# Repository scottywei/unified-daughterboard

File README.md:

unified-daughterboard-with-power-switch

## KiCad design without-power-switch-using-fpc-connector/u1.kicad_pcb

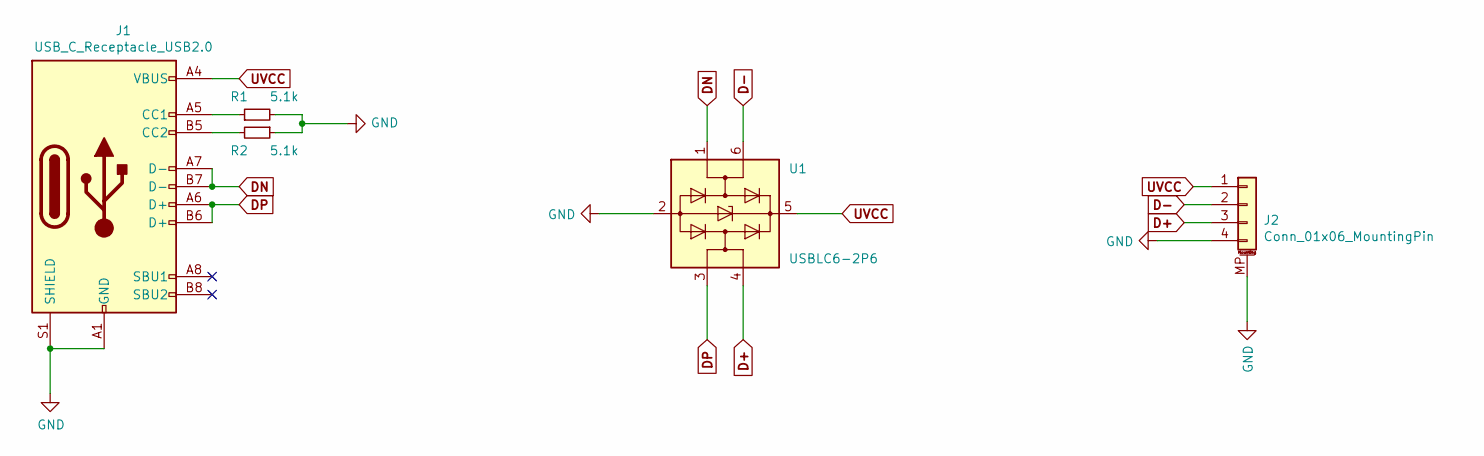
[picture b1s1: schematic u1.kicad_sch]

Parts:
J1: USB_C_Receptacle_USB2.0; USB_C_Receptacle_HRO_TYPE-C-31-M-12
J2: Conn_01x06_MountingPin; FPC_4P_1.0mm
R1, R2: 5.1k; R_0603_1608Metric
U1: USBLC6-2P6; SOT-666

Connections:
D+: J2.3, U1.4 (I/O2)
D-: J2.2, U1.6 (I/O1)
DN: J1.A7 (D-), J1.B7 (D-), U1.1 (I/O1)
DP: J1.A6 (D+), J1.B6 (D+), U1.3 (I/O2)
GND: J1.A1 (GND), J1.A12 (GND), J1.B1 (GND), J1.B12 (GND), J1.S1 (SHIELD), J2.4, J2.MP (MountPin), R1.2, R2.1, U1.2 (GND)
unnamed: J1.A5 (CC1), R1.1
unnamed: J1.B5 (CC2), R2.2
UVCC: J1.A4 (VBUS), J1.A9 (VBUS), J1.B4 (VBUS), J1.B9 (VBUS), J2.1, U1.5 (VBUS)

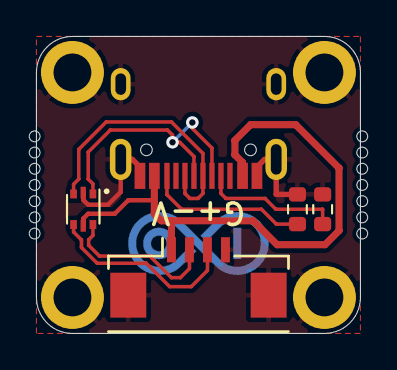
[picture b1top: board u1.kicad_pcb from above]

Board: 2 copper layers, 18.0 x 16.5 mm, 5 parts (0 on the bottom side), 8 nets.

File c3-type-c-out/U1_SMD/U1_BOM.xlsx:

编号 | 值/型号 | 封装 | 数量 | 备注
J1 | USB_C_Receptacle_USB2.0 | USB_C_Receptacle_HRO_TYPE-C-31-M-12 | 1 | https://www.usb.org/sites/default/files/documents/usb_type-c.zip
J2 | JST_SH_SM04B-SRSS | JST_SH_SM04B-SRSS-TB_1x04-1MP_P1.00mm_Horizontal | 1 | ~
R1, R2 | 5.1k | R_0603 | 2 | ~
U1 | USBLC6-2P6 | SOT-666 | 1 | https://www.st.com/resource/en/datasheet/usblc6-2.pdf

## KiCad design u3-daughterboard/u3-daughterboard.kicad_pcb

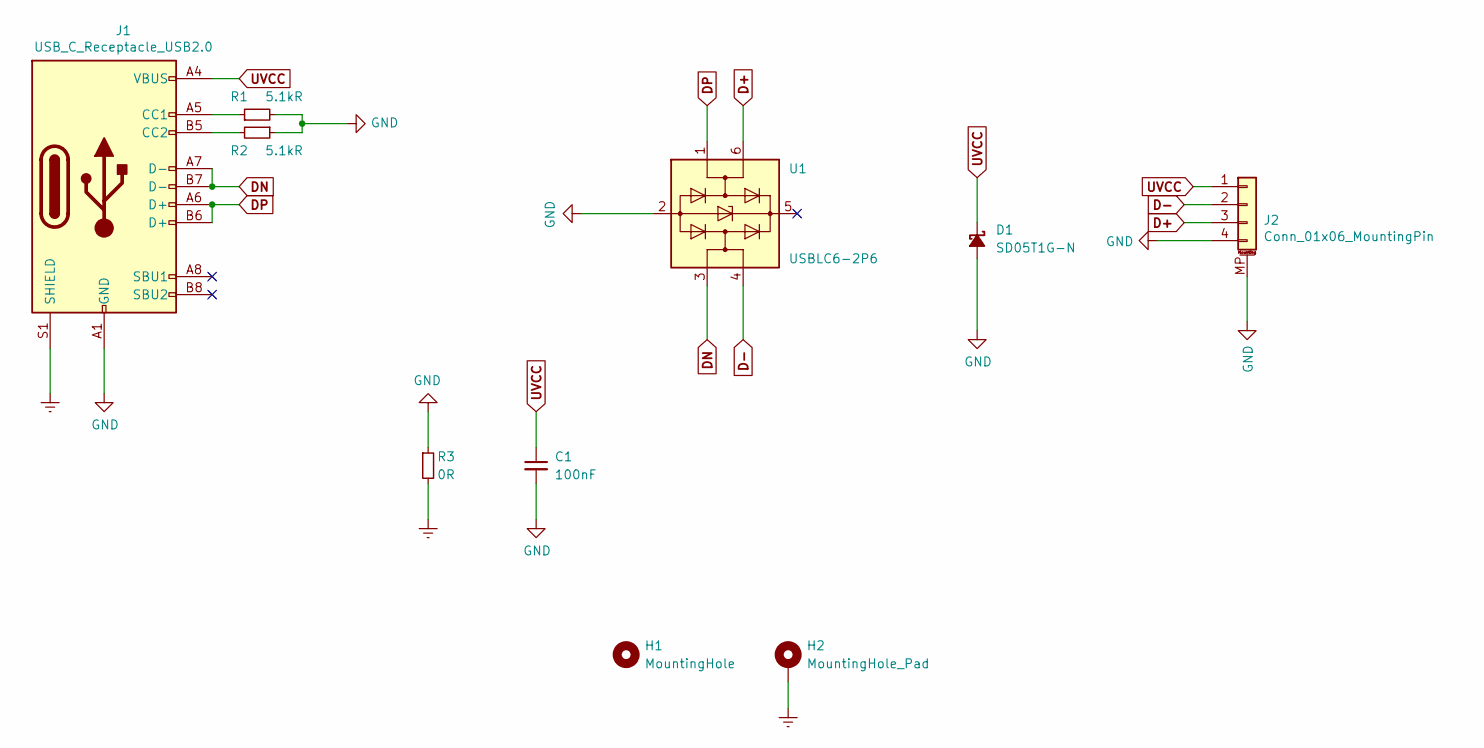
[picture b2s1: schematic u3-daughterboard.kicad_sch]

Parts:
C1: 100nF; C_0402_1005Metric
D1: SD05T1G-N; D_SOD-323
H1: MountingHole; MountingHole_3.2mm_M3
H2: MountingHole_Pad; MountingHole_3.2mm_M3_Pad_TopBottom
J1: USB_C_Receptacle_USB2.0; USB_C_Receptacle_HRO_TYPE-C-31-M-12
J2: Conn_01x06_MountingPin; molex_781710004
R1, R2: 5.1kR; R_0402_1005Metric
R3: 0R; R_0603_1608Metric
U1: USBLC6-2P6; SOT-666

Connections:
D+: J2.3, U1.6 (I/O1)
D-: J2.2, U1.4 (I/O2)
DN: J1.A7 (D-), J1.B7 (D-), U1.3 (I/O2)
DP: J1.A6 (D+), J1.B6 (D+), U1.1 (I/O1)
Earth: H2.1, J1.S1 (SHIELD), R3.2
GND: C1.2, D1.2 (A), J1.A1 (GND), J1.A12 (GND), J1.B1 (GND), J1.B12 (GND), J2.4, J2.MP (MountPin), R1.2, R2.1, R3.1, U1.2 (GND)
unnamed: J1.A5 (CC1), R1.1
unnamed: J1.B5 (CC2), R2.2
UVCC: C1.1, D1.1 (K), J1.A4 (VBUS), J1.A9 (VBUS), J1.B4 (VBUS), J1.B9 (VBUS), J2.1

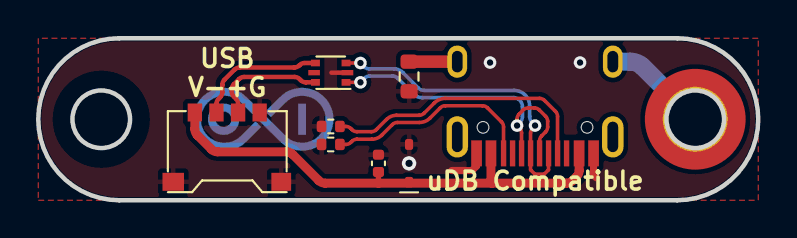
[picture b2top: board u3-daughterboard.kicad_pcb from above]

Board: 2 copper layers, 40.0 x 9.0 mm, 10 parts (0 on the bottom side), 9 nets.

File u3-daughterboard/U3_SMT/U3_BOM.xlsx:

位号 | 值/型号 | 封装 | 数量 | 备注 | Sourced | Model
C1 | 100nF | C_0402 | 1
R1, R2 | 5.1kR | R_0402 | 2
R3 | 0R | R_0603 | 1
D1 | SD05T1G-N | D_SOD-323 | 1
U1 | USBLC6-2P6 | SOT-666 | 1
J1 | USB_C_Receptacle_USB2.0 | USB_C_Receptacle_HRO_TYPE-C-31-M-12 | 1
J2 | molex_781710004 | molex_781710004 | 1

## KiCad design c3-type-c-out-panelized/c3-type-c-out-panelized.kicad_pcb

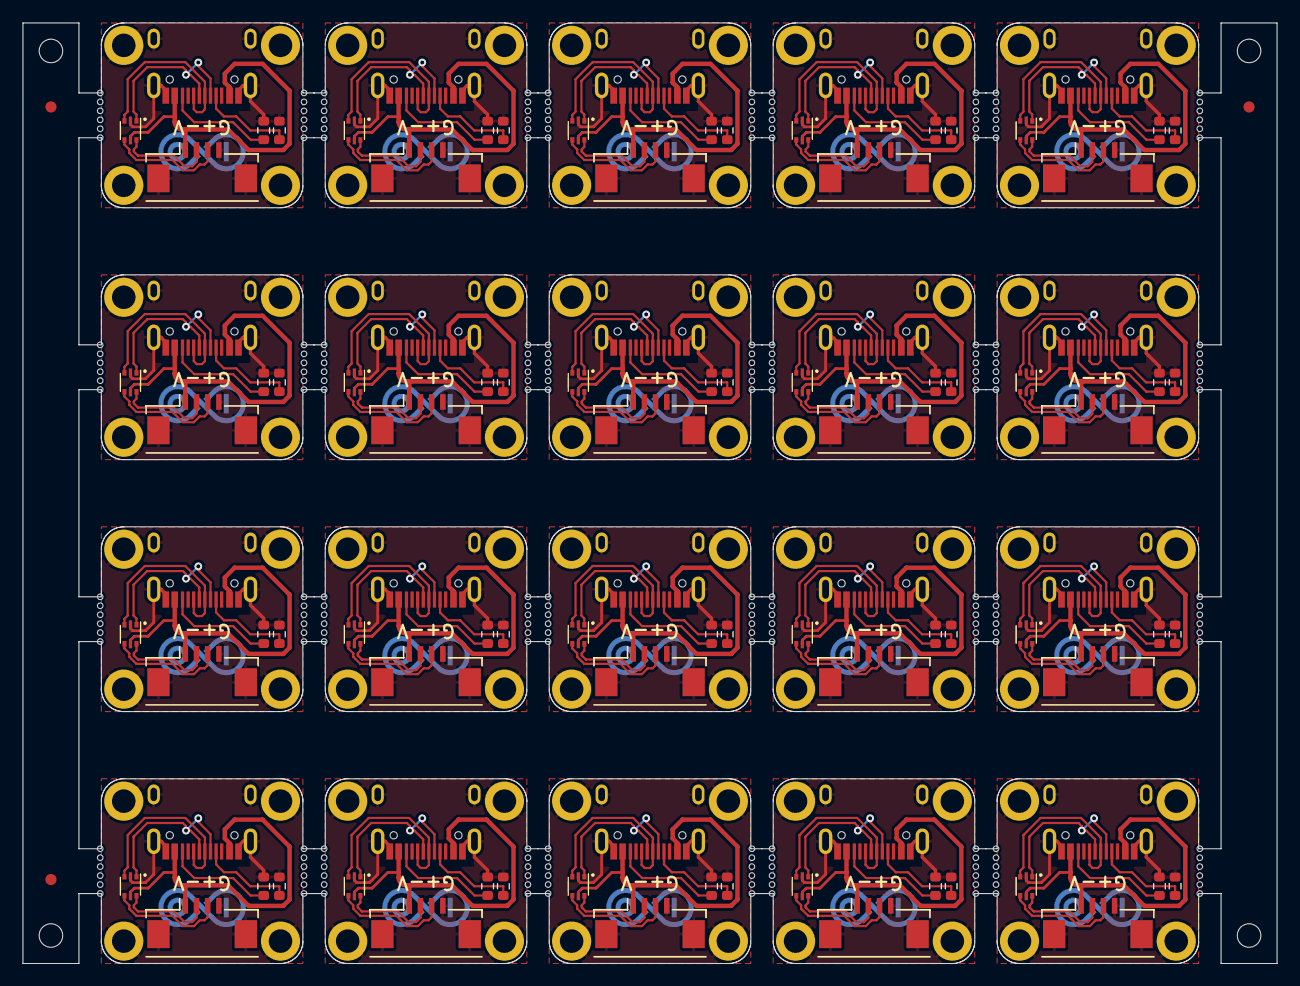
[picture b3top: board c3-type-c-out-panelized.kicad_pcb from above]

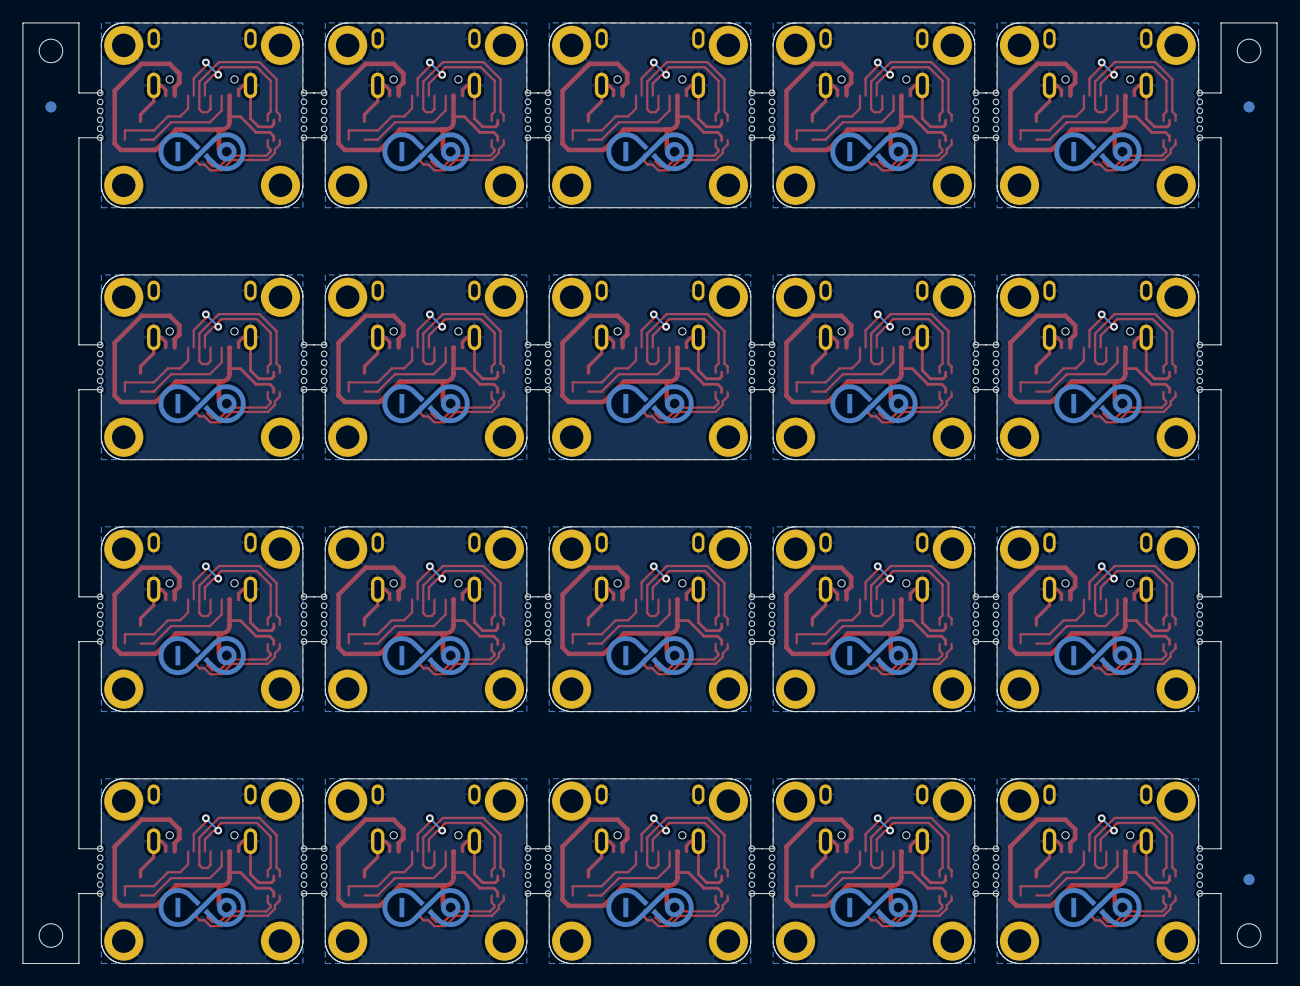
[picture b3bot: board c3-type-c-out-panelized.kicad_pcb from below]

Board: 2 copper layers, 112.0 x 84.0 mm, 350 parts (3 on the bottom side), 160 nets.

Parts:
J1, J1#2, J1#3, J1#4, J1#5, J1#6, J1#7, J1#8, J1#9, J1#10, J1#11, J1#12, J1#13, J1#14, J1#15, J1#16, J1#17, J1#18, J1#19, J1#20: USB_C_Receptacle_USB2.0; USB_C_Receptacle_HRO_TYPE-C-31-M-12
J2, J2#2, J2#3, J2#4, J2#5, J2#6, J2#7, J2#8, J2#9, J2#10, J2#11, J2#12, J2#13, J2#14, J2#15, J2#16, J2#17, J2#18, J2#19, J2#20: Conn_01x06_MountingPin; FPC_4P_1.0mm
KiKit_FID_B_1, KiKit_FID_B_2, KiKit_FID_B_3: Fiducial
KiKit_FID_T_1, KiKit_FID_T_2, KiKit_FID_T_3: Fiducial
KiKit_MB_1_1, KiKit_MB_1_2, KiKit_MB_1_3, KiKit_MB_1_4, KiKit_MB_1_5, KiKit_MB_1_6, KiKit_MB_2_1, KiKit_MB_2_2, KiKit_MB_2_3, KiKit_MB_2_4, KiKit_MB_2_5, KiKit_MB_2_6, KiKit_MB_3_1, KiKit_MB_3_2, KiKit_MB_3_3, KiKit_MB_3_4, KiKit_MB_3_5, KiKit_MB_3_6, KiKit_MB_4_1, KiKit_MB_4_2, KiKit_MB_4_3, KiKit_MB_4_4, KiKit_MB_4_5, KiKit_MB_4_6, KiKit_MB_5_1, KiKit_MB_5_2, KiKit_MB_5_3, KiKit_MB_5_4, KiKit_MB_5_5, KiKit_MB_5_6, KiKit_MB_6_1, KiKit_MB_6_2, KiKit_MB_6_3, KiKit_MB_6_4, KiKit_MB_6_5, KiKit_MB_6_6, KiKit_MB_7_1, KiKit_MB_7_2, KiKit_MB_7_3, KiKit_MB_7_4, KiKit_MB_7_5, KiKit_MB_7_6, KiKit_MB_8_1, KiKit_MB_8_2, KiKit_MB_8_3, KiKit_MB_8_4, KiKit_MB_8_5, KiKit_MB_8_6, KiKit_MB_9_1, KiKit_MB_9_2, KiKit_MB_9_3, KiKit_MB_9_4, KiKit_MB_9_5, KiKit_MB_9_6, KiKit_MB_10_1, KiKit_MB_10_2, KiKit_MB_10_3, KiKit_MB_10_4, KiKit_MB_10_5, KiKit_MB_10_6, KiKit_MB_11_1, KiKit_MB_11_2, KiKit_MB_11_3, KiKit_MB_11_4, KiKit_MB_11_5, KiKit_MB_11_6, KiKit_MB_12_1, KiKit_MB_12_2, KiKit_MB_12_3, KiKit_MB_12_4, KiKit_MB_12_5, KiKit_MB_12_6, KiKit_MB_13_1, KiKit_MB_13_2, KiKit_MB_13_3, KiKit_MB_13_4, KiKit_MB_13_5, KiKit_MB_13_6, KiKit_MB_14_1, KiKit_MB_14_2, KiKit_MB_14_3, KiKit_MB_14_4, KiKit_MB_14_5, KiKit_MB_14_6, KiKit_MB_15_1, KiKit_MB_15_2, KiKit_MB_15_3, KiKit_MB_15_4, KiKit_MB_15_5, KiKit_MB_15_6, KiKit_MB_16_1, KiKit_MB_16_2, KiKit_MB_16_3, KiKit_MB_16_4, KiKit_MB_16_5, KiKit_MB_16_6, KiKit_MB_17_1, KiKit_MB_17_2, KiKit_MB_17_3, KiKit_MB_17_4, KiKit_MB_17_5, KiKit_MB_17_6, KiKit_MB_18_1, KiKit_MB_18_2, KiKit_MB_18_3, KiKit_MB_18_4, KiKit_MB_18_5, KiKit_MB_18_6, KiKit_MB_19_1, KiKit_MB_19_2, KiKit_MB_19_3, KiKit_MB_19_4, KiKit_MB_19_5, KiKit_MB_19_6, KiKit_MB_20_1, KiKit_MB_20_2, KiKit_MB_20_3, KiKit_MB_20_4, KiKit_MB_20_5, KiKit_MB_20_6, KiKit_MB_21_1, KiKit_MB_21_2, KiKit_MB_21_3, KiKit_MB_21_4, KiKit_MB_21_5, KiKit_MB_21_6, KiKit_MB_22_1, KiKit_MB_22_2, KiKit_MB_22_3, KiKit_MB_22_4, KiKit_MB_22_5, KiKit_MB_22_6, KiKit_MB_23_1, KiKit_MB_23_2, KiKit_MB_23_3, KiKit_MB_23_4, KiKit_MB_23_5, KiKit_MB_23_6, KiKit_MB_24_1, KiKit_MB_24_2, KiKit_MB_24_3, KiKit_MB_24_4, KiKit_MB_24_5, KiKit_MB_24_6, KiKit_MB_25_1, KiKit_MB_25_2, KiKit_MB_25_3, KiKit_MB_25_4, KiKit_MB_25_5, KiKit_MB_25_6, KiKit_MB_26_1, KiKit_MB_26_2, KiKit_MB_26_3, KiKit_MB_26_4, KiKit_MB_26_5, KiKit_MB_26_6, KiKit_MB_27_1, KiKit_MB_27_2, KiKit_MB_27_3, KiKit_MB_27_4, KiKit_MB_27_5, KiKit_MB_27_6, KiKit_MB_28_1, KiKit_MB_28_2, KiKit_MB_28_3, KiKit_MB_28_4, KiKit_MB_28_5, KiKit_MB_28_6, KiKit_MB_29_1, KiKit_MB_29_2, KiKit_MB_29_3, KiKit_MB_29_4, KiKit_MB_29_5, KiKit_MB_29_6, KiKit_MB_30_1, KiKit_MB_30_2, KiKit_MB_30_3, KiKit_MB_30_4, KiKit_MB_30_5, KiKit_MB_30_6, KiKit_MB_31_1, KiKit_MB_31_2, KiKit_MB_31_3, KiKit_MB_31_4, KiKit_MB_31_5, KiKit_MB_31_6, KiKit_MB_32_1, KiKit_MB_32_2, KiKit_MB_32_3, KiKit_MB_32_4, KiKit_MB_32_5, KiKit_MB_32_6, KiKit_MB_33_1, KiKit_MB_33_2, KiKit_MB_33_3, KiKit_MB_33_4, KiKit_MB_33_5, KiKit_MB_33_6, KiKit_MB_34_1, KiKit_MB_34_2, KiKit_MB_34_3, KiKit_MB_34_4, KiKit_MB_34_5, KiKit_MB_34_6, KiKit_MB_35_1, KiKit_MB_35_2, KiKit_MB_35_3, KiKit_MB_35_4, KiKit_MB_35_5, KiKit_MB_35_6, KiKit_MB_36_1, KiKit_MB_36_2, KiKit_MB_36_3, KiKit_MB_36_4, KiKit_MB_36_5, KiKit_MB_36_6, KiKit_MB_37_1, KiKit_MB_37_2, KiKit_MB_37_3, KiKit_MB_37_4, KiKit_MB_37_5, KiKit_MB_37_6, KiKit_MB_38_1, KiKit_MB_38_2, KiKit_MB_38_3, KiKit_MB_38_4, KiKit_MB_38_5, KiKit_MB_38_6, KiKit_MB_39_1, KiKit_MB_39_2, KiKit_MB_39_3, KiKit_MB_39_4, KiKit_MB_39_5, KiKit_MB_39_6, KiKit_MB_40_1, KiKit_MB_40_2, KiKit_MB_40_3, KiKit_MB_40_4, KiKit_MB_40_5, KiKit_MB_40_6: NPTH
KiKit_TO_1, KiKit_TO_2, KiKit_TO_3, KiKit_TO_4: NPTH
R1, R1#2, R1#3, R1#4, R1#5, R1#6, R1#7, R1#8, R1#9, R1#10, R1#11, R1#12, R1#13, R1#14, R1#15, R1#16, R1#17, R1#18, R1#19, R1#20, R2, R2#2, R2#3, R2#4, R2#5, R2#6, R2#7, R2#8, R2#9, R2#10, R2#11, R2#12, R2#13, R2#14, R2#15, R2#16, R2#17, R2#18, R2#19, R2#20: 5.1k; R_0603_1608Metric
U1, U1#2, U1#3, U1#4, U1#5, U1#6, U1#7, U1#8, U1#9, U1#10, U1#11, U1#12, U1#13, U1#14, U1#15, U1#16, U1#17, U1#18, U1#19, U1#20: USBLC6-2P6; SOT-666

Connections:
Board_0-D+: J2#13.3, U1#12.4 (I/O2)
Board_0-D-: J2#13.2, U1#12.6 (I/O1)
Board_0-DN: J1#6.A7 (D-), J1#6.B7 (D-), U1#12.1 (I/O1)
Board_0-DP: J1#6.A6 (D+), J1#6.B6 (D+), U1#12.3 (I/O2)
Board_0-GND: J1#6.A1 (GND), J1#6.A12 (GND), J1#6.B1 (GND), J1#6.B12 (GND), J1#6.S1 (SHIELD), J2#13.4, J2#13.MP (MountPin), R1#14.2, R2#15.1, U1#12.2 (GND)
Board_0-Net-(J1-CC1): J1#6.A5 (CC1), R1#14.1
Board_0-Net-(J1-CC2): J1#6.B5 (CC2), R2#15.2
Board_0-UVCC: J1#6.A4 (VBUS), J1#6.A9 (VBUS), J1#6.B4 (VBUS), J1#6.B9 (VBUS), J2#13.1, U1#12.5 (VBUS)
Board_1-D+: J2#18.3, U1#18.4 (I/O2)
Board_1-D-: J2#18.2, U1#18.6 (I/O1)
Board_1-DN: J1#17.A7 (D-), J1#17.B7 (D-), U1#18.1 (I/O1)
Board_1-DP: J1#17.A6 (D+), J1#17.B6 (D+), U1#18.3 (I/O2)
Board_1-GND: J1#17.A1 (GND), J1#17.A12 (GND), J1#17.B1 (GND), J1#17.B12 (GND), J1#17.S1 (SHIELD), J2#18.4, J2#18.MP (MountPin), R1#11.2, R2#16.1, U1#18.2 (GND)
Board_1-Net-(J1-CC1): J1#17.A5 (CC1), R1#11.1
Board_1-Net-(J1-CC2): J1#17.B5 (CC2), R2#16.2
Board_1-UVCC: J1#17.A4 (VBUS), J1#17.A9 (VBUS), J1#17.B4 (VBUS), J1#17.B9 (VBUS), J2#18.1, U1#18.5 (VBUS)
Board_2-D+: J2#14.3, U1#7.4 (I/O2)
Board_2-D-: J2#14.2, U1#7.6 (I/O1)
Board_2-DN: J1#20.A7 (D-), J1#20.B7 (D-), U1#7.1 (I/O1)
Board_2-DP: J1#20.A6 (D+), J1#20.B6 (D+), U1#7.3 (I/O2)
Board_2-GND: J1#20.A1 (GND), J1#20.A12 (GND), J1#20.B1 (GND), J1#20.B12 (GND), J1#20.S1 (SHIELD), J2#14.4, J2#14.MP (MountPin), R1#3.2, R2#18.1, U1#7.2 (GND)
Board_2-Net-(J1-CC1): J1#20.A5 (CC1), R1#3.1
Board_2-Net-(J1-CC2): J1#20.B5 (CC2), R2#18.2
Board_2-UVCC: J1#20.A4 (VBUS), J1#20.A9 (VBUS), J1#20.B4 (VBUS), J1#20.B9 (VBUS), J2#14.1, U1#7.5 (VBUS)
Board_3-D+: J2#11.3, U1#13.4 (I/O2)
Board_3-D-: J2#11.2, U1#13.6 (I/O1)
Board_3-DN: J1#8.A7 (D-), J1#8.B7 (D-), U1#13.1 (I/O1)
Board_3-DP: J1#8.A6 (D+), J1#8.B6 (D+), U1#13.3 (I/O2)
Board_3-GND: J1#8.A1 (GND), J1#8.A12 (GND), J1#8.B1 (GND), J1#8.B12 (GND), J1#8.S1 (SHIELD), J2#11.4, J2#11.MP (MountPin), R1#5.2, R2#4.1, U1#13.2 (GND)
Board_3-Net-(J1-CC1): J1#8.A5 (CC1), R1#5.1
Board_3-Net-(J1-CC2): J1#8.B5 (CC2), R2#4.2
Board_3-UVCC: J1#8.A4 (VBUS), J1#8.A9 (VBUS), J1#8.B4 (VBUS), J1#8.B9 (VBUS), J2#11.1, U1#13.5 (VBUS)
Board_4-D+: J2#2.3, U1#10.4 (I/O2)
Board_4-D-: J2#2.2, U1#10.6 (I/O1)
Board_4-DN: J1#10.A7 (D-), J1#10.B7 (D-), U1#10.1 (I/O1)
Board_4-DP: J1#10.A6 (D+), J1#10.B6 (D+), U1#10.3 (I/O2)
Board_4-GND: J1#10.A1 (GND), J1#10.A12 (GND), J1#10.B1 (GND), J1#10.B12 (GND), J1#10.S1 (SHIELD), J2#2.4, J2#2.MP (MountPin), R1#8.2, R2#11.1, U1#10.2 (GND)
Board_4-Net-(J1-CC1): J1#10.A5 (CC1), R1#8.1
Board_4-Net-(J1-CC2): J1#10.B5 (CC2), R2#11.2
Board_4-UVCC: J1#10.A4 (VBUS), J1#10.A9 (VBUS), J1#10.B4 (VBUS), J1#10.B9 (VBUS), J2#2.1, U1#10.5 (VBUS)
Board_5-D+: J2#15.3, U1#11.4 (I/O2)
Board_5-D-: J2#15.2, U1#11.6 (I/O1)
Board_5-DN: J1#3.A7 (D-), J1#3.B7 (D-), U1#11.1 (I/O1)
Board_5-DP: J1#3.A6 (D+), J1#3.B6 (D+), U1#11.3 (I/O2)
Board_5-GND: J1#3.A1 (GND), J1#3.A12 (GND), J1#3.B1 (GND), J1#3.B12 (GND), J1#3.S1 (SHIELD), J2#15.4, J2#15.MP (MountPin), R1#16.2, R2#6.1, U1#11.2 (GND)
Board_5-Net-(J1-CC1): J1#3.A5 (CC1), R1#16.1
Board_5-Net-(J1-CC2): J1#3.B5 (CC2), R2#6.2
Board_5-UVCC: J1#3.A4 (VBUS), J1#3.A9 (VBUS), J1#3.B4 (VBUS), J1#3.B9 (VBUS), J2#15.1, U1#11.5 (VBUS)
Board_6-D+: J2#20.3, U1#5.4 (I/O2)
Board_6-D-: J2#20.2, U1#5.6 (I/O1)
Board_6-DN: J1#9.A7 (D-), J1#9.B7 (D-), U1#5.1 (I/O1)
Board_6-DP: J1#9.A6 (D+), J1#9.B6 (D+), U1#5.3 (I/O2)
Board_6-GND: J1#9.A1 (GND), J1#9.A12 (GND), J1#9.B1 (GND), J1#9.B12 (GND), J1#9.S1 (SHIELD), J2#20.4, J2#20.MP (MountPin), R1#15.2, R2#19.1, U1#5.2 (GND)
Board_6-Net-(J1-CC1): J1#9.A5 (CC1), R1#15.1
Board_6-Net-(J1-CC2): J1#9.B5 (CC2), R2#19.2
Board_6-UVCC: J1#9.A4 (VBUS), J1#9.A9 (VBUS), J1#9.B4 (VBUS), J1#9.B9 (VBUS), J2#20.1, U1#5.5 (VBUS)
Board_7-D+: J2#5.3, U1#4.4 (I/O2)
Board_7-D-: J2#5.2, U1#4.6 (I/O1)
Board_7-DN: J1#15.A7 (D-), J1#15.B7 (D-), U1#4.1 (I/O1)
Board_7-DP: J1#15.A6 (D+), J1#15.B6 (D+), U1#4.3 (I/O2)
Board_7-GND: J1#15.A1 (GND), J1#15.A12 (GND), J1#15.B1 (GND), J1#15.B12 (GND), J1#15.S1 (SHIELD), J2#5.4, J2#5.MP (MountPin), R1#10.2, R2#13.1, U1#4.2 (GND)
Board_7-Net-(J1-CC1): J1#15.A5 (CC1), R1#10.1
Board_7-Net-(J1-CC2): J1#15.B5 (CC2), R2#13.2
Board_7-UVCC: J1#15.A4 (VBUS), J1#15.A9 (VBUS), J1#15.B4 (VBUS), J1#15.B9 (VBUS), J2#5.1, U1#4.5 (VBUS)
Board_8-D+: J2#10.3, U1#2.4 (I/O2)
Board_8-D-: J2#10.2, U1#2.6 (I/O1)
Board_8-DN: J1#2.A7 (D-), J1#2.B7 (D-), U1#2.1 (I/O1)
Board_8-DP: J1#2.A6 (D+), J1#2.B6 (D+), U1#2.3 (I/O2)
Board_8-GND: J1#2.A1 (GND), J1#2.A12 (GND), J1#2.B1 (GND), J1#2.B12 (GND), J1#2.S1 (SHIELD), J2#10.4, J2#10.MP (MountPin), R1#18.2, R2#12.1, U1#2.2 (GND)
Board_8-Net-(J1-CC1): J1#2.A5 (CC1), R1#18.1
Board_8-Net-(J1-CC2): J1#2.B5 (CC2), R2#12.2
Board_8-UVCC: J1#2.A4 (VBUS), J1#2.A9 (VBUS), J1#2.B4 (VBUS), J1#2.B9 (VBUS), J2#10.1, U1#2.5 (VBUS)
Board_9-D+: J2#6.3, U1#16.4 (I/O2)
Board_9-D-: J2#6.2, U1#16.6 (I/O1)
Board_9-DN: J1#14.A7 (D-), J1#14.B7 (D-), U1#16.1 (I/O1)
Board_9-DP: J1#14.A6 (D+), J1#14.B6 (D+), U1#16.3 (I/O2)
Board_9-GND: J1#14.A1 (GND), J1#14.A12 (GND), J1#14.B1 (GND), J1#14.B12 (GND), J1#14.S1 (SHIELD), J2#6.4, J2#6.MP (MountPin), R1#13.2, R2#10.1, U1#16.2 (GND)
Board_9-Net-(J1-CC1): J1#14.A5 (CC1), R1#13.1
Board_9-Net-(J1-CC2): J1#14.B5 (CC2), R2#10.2
Board_9-UVCC: J1#14.A4 (VBUS), J1#14.A9 (VBUS), J1#14.B4 (VBUS), J1#14.B9 (VBUS), J2#6.1, U1#16.5 (VBUS)
Board_10-D+: J2#16.3, U1#6.4 (I/O2)
Board_10-D-: J2#16.2, U1#6.6 (I/O1)
Board_10-DN: J1#12.A7 (D-), J1#12.B7 (D-), U1#6.1 (I/O1)
Board_10-DP: J1#12.A6 (D+), J1#12.B6 (D+), U1#6.3 (I/O2)
Board_10-GND: J1#12.A1 (GND), J1#12.A12 (GND), J1#12.B1 (GND), J1#12.B12 (GND), J1#12.S1 (SHIELD), J2#16.4, J2#16.MP (MountPin), R1#7.2, R2#17.1, U1#6.2 (GND)
Board_10-Net-(J1-CC1): J1#12.A5 (CC1), R1#7.1
Board_10-Net-(J1-CC2): J1#12.B5 (CC2), R2#17.2
Board_10-UVCC: J1#12.A4 (VBUS), J1#12.A9 (VBUS), J1#12.B4 (VBUS), J1#12.B9 (VBUS), J2#16.1, U1#6.5 (VBUS)
Board_11-D+: J2#19.3, U1#17.4 (I/O2)
Board_11-D-: J2#19.2, U1#17.6 (I/O1)
Board_11-DN: J1.A7 (D-), J1.B7 (D-), U1#17.1 (I/O1)
Board_11-DP: J1.A6 (D+), J1.B6 (D+), U1#17.3 (I/O2)
Board_11-GND: J1.A1 (GND), J1.A12 (GND), J1.B1 (GND), J1.B12 (GND), J1.S1 (SHIELD), J2#19.4, J2#19.MP (MountPin), R1#19.2, R2#20.1, U1#17.2 (GND)
Board_11-Net-(J1-CC1): J1.A5 (CC1), R1#19.1
Board_11-Net-(J1-CC2): J1.B5 (CC2), R2#20.2
Board_11-UVCC: J1.A4 (VBUS), J1.A9 (VBUS), J1.B4 (VBUS), J1.B9 (VBUS), J2#19.1, U1#17.5 (VBUS)
Board_12-D+: J2.3, U1#14.4 (I/O2)
Board_12-D-: J2.2, U1#14.6 (I/O1)
Board_12-DN: J1#4.A7 (D-), J1#4.B7 (D-), U1#14.1 (I/O1)
Board_12-DP: J1#4.A6 (D+), J1#4.B6 (D+), U1#14.3 (I/O2)
Board_12-GND: J1#4.A1 (GND), J1#4.A12 (GND), J1#4.B1 (GND), J1#4.B12 (GND), J1#4.S1 (SHIELD), J2.4, J2.MP (MountPin), R1#12.2, R2#9.1, U1#14.2 (GND)
Board_12-Net-(J1-CC1): J1#4.A5 (CC1), R1#12.1
Board_12-Net-(J1-CC2): J1#4.B5 (CC2), R2#9.2
Board_12-UVCC: J1#4.A4 (VBUS), J1#4.A9 (VBUS), J1#4.B4 (VBUS), J1#4.B9 (VBUS), J2.1, U1#14.5 (VBUS)
Board_13-D+: J2#9.3, U1#3.4 (I/O2)
Board_13-D-: J2#9.2, U1#3.6 (I/O1)
Board_13-DN: J1#7.A7 (D-), J1#7.B7 (D-), U1#3.1 (I/O1)
Board_13-DP: J1#7.A6 (D+), J1#7.B6 (D+), U1#3.3 (I/O2)
Board_13-GND: J1#7.A1 (GND), J1#7.A12 (GND), J1#7.B1 (GND), J1#7.B12 (GND), J1#7.S1 (SHIELD), J2#9.4, J2#9.MP (MountPin), R1#2.2, R2#5.1, U1#3.2 (GND)
Board_13-Net-(J1-CC1): J1#7.A5 (CC1), R1#2.1
Board_13-Net-(J1-CC2): J1#7.B5 (CC2), R2#5.2
Board_13-UVCC: J1#7.A4 (VBUS), J1#7.A9 (VBUS), J1#7.B4 (VBUS), J1#7.B9 (VBUS), J2#9.1, U1#3.5 (VBUS)
Board_14-D+: J2#8.3, U1#20.4 (I/O2)
Board_14-D-: J2#8.2, U1#20.6 (I/O1)
Board_14-DN: J1#18.A7 (D-), J1#18.B7 (D-), U1#20.1 (I/O1)
Board_14-DP: J1#18.A6 (D+), J1#18.B6 (D+), U1#20.3 (I/O2)
Board_14-GND: J1#18.A1 (GND), J1#18.A12 (GND), J1#18.B1 (GND), J1#18.B12 (GND), J1#18.S1 (SHIELD), J2#8.4, J2#8.MP (MountPin), R1.2, R2#8.1, U1#20.2 (GND)
Board_14-Net-(J1-CC1): J1#18.A5 (CC1), R1.1
Board_14-Net-(J1-CC2): J1#18.B5 (CC2), R2#8.2
Board_14-UVCC: J1#18.A4 (VBUS), J1#18.A9 (VBUS), J1#18.B4 (VBUS), J1#18.B9 (VBUS), J2#8.1, U1#20.5 (VBUS)
Board_15-D+: J2#17.3, U1#15.4 (I/O2)
Board_15-D-: J2#17.2, U1#15.6 (I/O1)
Board_15-DN: J1#11.A7 (D-), J1#11.B7 (D-), U1#15.1 (I/O1)
Board_15-DP: J1#11.A6 (D+), J1#11.B6 (D+), U1#15.3 (I/O2)
Board_15-GND: J1#11.A1 (GND), J1#11.A12 (GND), J1#11.B1 (GND), J1#11.B12 (GND), J1#11.S1 (SHIELD), J2#17.4, J2#17.MP (MountPin), R1#20.2, R2#2.1, U1#15.2 (GND)
Board_15-Net-(J1-CC1): J1#11.A5 (CC1), R1#20.1
Board_15-Net-(J1-CC2): J1#11.B5 (CC2), R2#2.2
Board_15-UVCC: J1#11.A4 (VBUS), J1#11.A9 (VBUS), J1#11.B4 (VBUS), J1#11.B9 (VBUS), J2#17.1, U1#15.5 (VBUS)
Board_16-D+: J2#4.3, U1#9.4 (I/O2)
Board_16-D-: J2#4.2, U1#9.6 (I/O1)
Board_16-DN: J1#5.A7 (D-), J1#5.B7 (D-), U1#9.1 (I/O1)
Board_16-DP: J1#5.A6 (D+), J1#5.B6 (D+), U1#9.3 (I/O2)
Board_16-GND: J1#5.A1 (GND), J1#5.A12 (GND), J1#5.B1 (GND), J1#5.B12 (GND), J1#5.S1 (SHIELD), J2#4.4, J2#4.MP (MountPin), R1#17.2, R2.1, U1#9.2 (GND)
Board_16-Net-(J1-CC1): J1#5.A5 (CC1), R1#17.1
Board_16-Net-(J1-CC2): J1#5.B5 (CC2), R2.2
Board_16-UVCC: J1#5.A4 (VBUS), J1#5.A9 (VBUS), J1#5.B4 (VBUS), J1#5.B9 (VBUS), J2#4.1, U1#9.5 (VBUS)
Board_17-D+: J2#12.3, U1#8.4 (I/O2)
Board_17-D-: J2#12.2, U1#8.6 (I/O1)
Board_17-DN: J1#19.A7 (D-), J1#19.B7 (D-), U1#8.1 (I/O1)
Board_17-DP: J1#19.A6 (D+), J1#19.B6 (D+), U1#8.3 (I/O2)
Board_17-GND: J1#19.A1 (GND), J1#19.A12 (GND), J1#19.B1 (GND), J1#19.B12 (GND), J1#19.S1 (SHIELD), J2#12.4, J2#12.MP (MountPin), R1#9.2, R2#7.1, U1#8.2 (GND)
Board_17-Net-(J1-CC1): J1#19.A5 (CC1), R1#9.1
Board_17-Net-(J1-CC2): J1#19.B5 (CC2), R2#7.2
Board_17-UVCC: J1#19.A4 (VBUS), J1#19.A9 (VBUS), J1#19.B4 (VBUS), J1#19.B9 (VBUS), J2#12.1, U1#8.5 (VBUS)
Board_18-D+: J2#7.3, U1#19.4 (I/O2)
Board_18-D-: J2#7.2, U1#19.6 (I/O1)
Board_18-DN: J1#16.A7 (D-), J1#16.B7 (D-), U1#19.1 (I/O1)
Board_18-DP: J1#16.A6 (D+), J1#16.B6 (D+), U1#19.3 (I/O2)
Board_18-GND: J1#16.A1 (GND), J1#16.A12 (GND), J1#16.B1 (GND), J1#16.B12 (GND), J1#16.S1 (SHIELD), J2#7.4, J2#7.MP (MountPin), R1#6.2, R2#14.1, U1#19.2 (GND)
Board_18-Net-(J1-CC1): J1#16.A5 (CC1), R1#6.1
Board_18-Net-(J1-CC2): J1#16.B5 (CC2), R2#14.2
Board_18-UVCC: J1#16.A4 (VBUS), J1#16.A9 (VBUS), J1#16.B4 (VBUS), J1#16.B9 (VBUS), J2#7.1, U1#19.5 (VBUS)
Board_19-D+: J2#3.3, U1.4 (I/O2)
Board_19-D-: J2#3.2, U1.6 (I/O1)
Board_19-DN: J1#13.A7 (D-), J1#13.B7 (D-), U1.1 (I/O1)
Board_19-DP: J1#13.A6 (D+), J1#13.B6 (D+), U1.3 (I/O2)
Board_19-GND: J1#13.A1 (GND), J1#13.A12 (GND), J1#13.B1 (GND), J1#13.B12 (GND), J1#13.S1 (SHIELD), J2#3.4, J2#3.MP (MountPin), R1#4.2, R2#3.1, U1.2 (GND)
Board_19-Net-(J1-CC1): J1#13.A5 (CC1), R1#4.1
Board_19-Net-(J1-CC2): J1#13.B5 (CC2), R2#3.2
Board_19-UVCC: J1#13.A4 (VBUS), J1#13.A9 (VBUS), J1#13.B4 (VBUS), J1#13.B9 (VBUS), J2#3.1, U1.5 (VBUS)

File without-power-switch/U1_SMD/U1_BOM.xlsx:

位号/Designator | 型号/Comment | 封装/Footprint | 数量/Quantity | 备注/Description | 嘉立创元件编号
J1 | USB_C_Receptacle_USB2.0 | USB_C_Receptacle_HRO_TYPE-C-31-M-12 | 1 | 16Pin Type-C母座 | C709357
J2 | JST_SH_SM04B-SRSS | JST_SH_SM04B-SRSS-TB_1x04-1MP_P1.00mm_Horizontal | 1 | SH 4Pin端子插座 | C2764183
R1, R2 | 5.1kΩ | R_0603 | 2 | 5%贴片电阻
U1 | USBLC6-2P6 | SOT-666 | 1 | ESD芯片 | C2827693

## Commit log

2021-06-03 rev1
2021-06-24 Update PCB design files
2021-07-09 Update projects structure
2021-07-09 Add warped design
2021-07-14 Add production files
2021-08-17 Add Percent Studio Mod version
2022-06-23 Fix Percent Studio Mod version design
2022-08-23 Add molex connector version
2022-10-19 Add U1 model
2022-11-13 Update Percent Mod KiCad project version
2022-11-14 Add rendering files
2022-12-07 Update U1 panelized production files
2023-06-15 Add U3 design
2023-06-17 Finish U3 design
2023-07-03 Finish U3 daughterboard production files
2023-07-04 Update U3 design files and add production files
2023-07-18 Update U3 SMT production files
2023-07-23 Update U3 BOM status
2024-08-04 Add FPC connector version
2024-08-26 Add C3 FPC version production files
2024-08-27 Submit prototype production files
2024-09-08 Add stencils design for C3 FPC version
2024-11-25 Submit C3 Type-C Mod production files
2024-12-22 Add C3 mod version panelized production files
2025-01-05 Add new U1 panelized production files
2025-06-16 Update model of U1 with FPC connector
